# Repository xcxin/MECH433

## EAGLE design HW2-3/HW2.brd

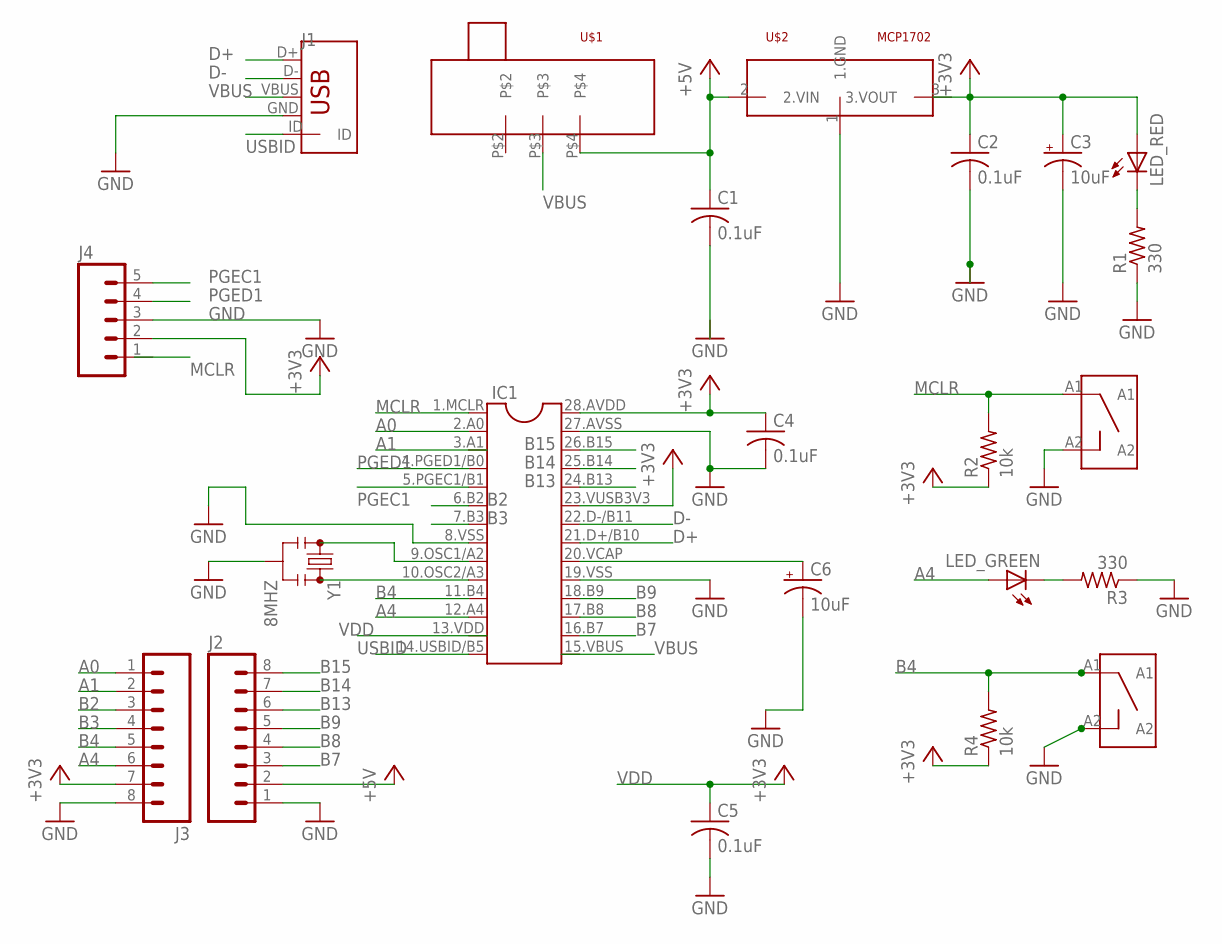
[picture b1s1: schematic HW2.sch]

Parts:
C1, C2, C4, C5: 0.1uF; C025-024X044
C3, C6: 10uF; B45181A
IC1: DIL28-3
J1: USB-MB-H
J2, J3: M08; 1X08_ROUND
J4: M05PTH; 1X05
LED_GREEN: LED3MM
LED_RED: LED3MM
R1, R3: 330; 0207/10
R2, R4: 10k; 0207/10
U$1: SLIDE_SWITCH
U$2: MCP1702; TO92
U$4, U$5: PUSH_BUTTON; RDT1034
Y1: 8MHZ; RESONATOR-PTH

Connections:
+3V3: C2.1, C3.+, C4.1, IC1.23.VUSB3V3 (23), IC1.28.AVDD (28), J3.7, J4.2, LED_RED.A, R2.1, R4.1
+5V: C1.1, J2.2, U$1.P$4, U$2.2 (2.VIN)
A0: IC1.2.A0 (2), J3.1
A1: J3.2
A4: IC1.12.A4 (12), J3.6, LED_GREEN.A
B2: IC1.6.B2 (6), J3.3
B3: IC1.7.B3 (7), J3.4
B4: IC1.11.B4 (11), J3.5, R4.2, U$4.A1
B7: IC1.16.B7 (16), J2.3
B8: IC1.17.B8 (17), J2.4
B9: IC1.18.B9 (18), J2.5
B13: IC1.24.B13 (24), J2.6
B14: IC1.25.B14 (25), J2.7
B15: IC1.26.B15 (26), J2.8
D+: IC1.21.D+/B10 (21), J1.D+
D-: IC1.22.D-/B11 (22), J1.D-
GND: C2.2, C3.-, C4.2, C5.2, C6.-, IC1.8.VSS (8), IC1.19.VSS (19), IC1.27.AVSS (27), J1.GND, J2.1, J3.8, J4.3, R1.1, R3.1, U$2.1 (1.GND), U$4.A2, U$5.A2, Y1.2
MCLR: IC1.1.MCLR, R2.2, U$5.A1
unnamed: LED_GREEN.K (C), R3.2
unnamed: IC1.9.OSC1/A2 (9), Y1.1
unnamed: LED_RED.K (C), R1.2
unnamed: IC1.10.OSC2/A3 (10), Y1.3
unnamed: C6.+, IC1.20.VCAP (20)
PGEC1: IC1.5.PGEC1/B1 (5), J4.5
PGED1: IC1.4.PGED1/B0 (4), J4.4
USBID: IC1.14.USBID/B5 (14), J1.ID
VBUS: J1.VBUS, U$1.P$3
VDD: C5.1

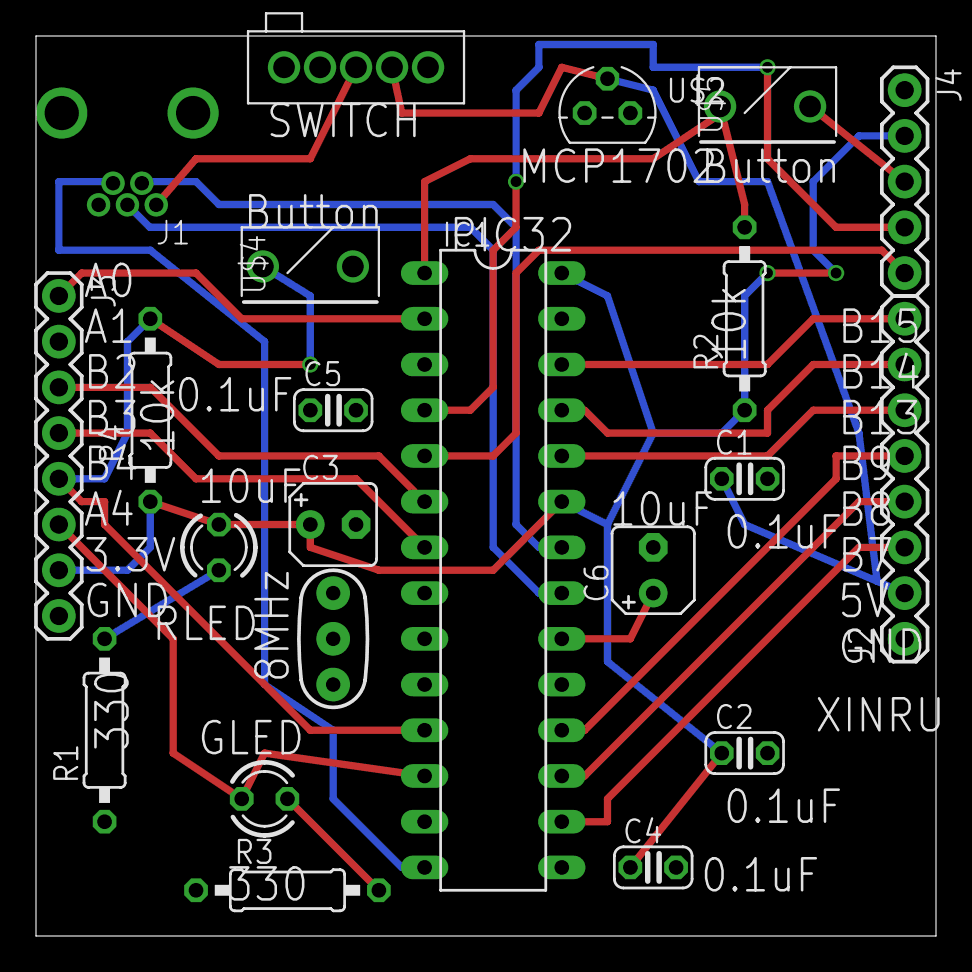
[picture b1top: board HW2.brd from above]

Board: 2 copper layers, 50.0 x 50.0 mm, 22 parts (0 on the bottom side), 26 nets.
